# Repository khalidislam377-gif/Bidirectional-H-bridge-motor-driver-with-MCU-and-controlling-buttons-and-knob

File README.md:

# Bidirectional-H-bridge-motor-driver-with-MCU-and-controlling-buttons-and-knob
`An embedded control architecture and discrete power stage for bidirectional DC motor regulation, featuring finite-state machine logic, real-time telemetry, and a Rev 1.0 hardware post-mortem.`

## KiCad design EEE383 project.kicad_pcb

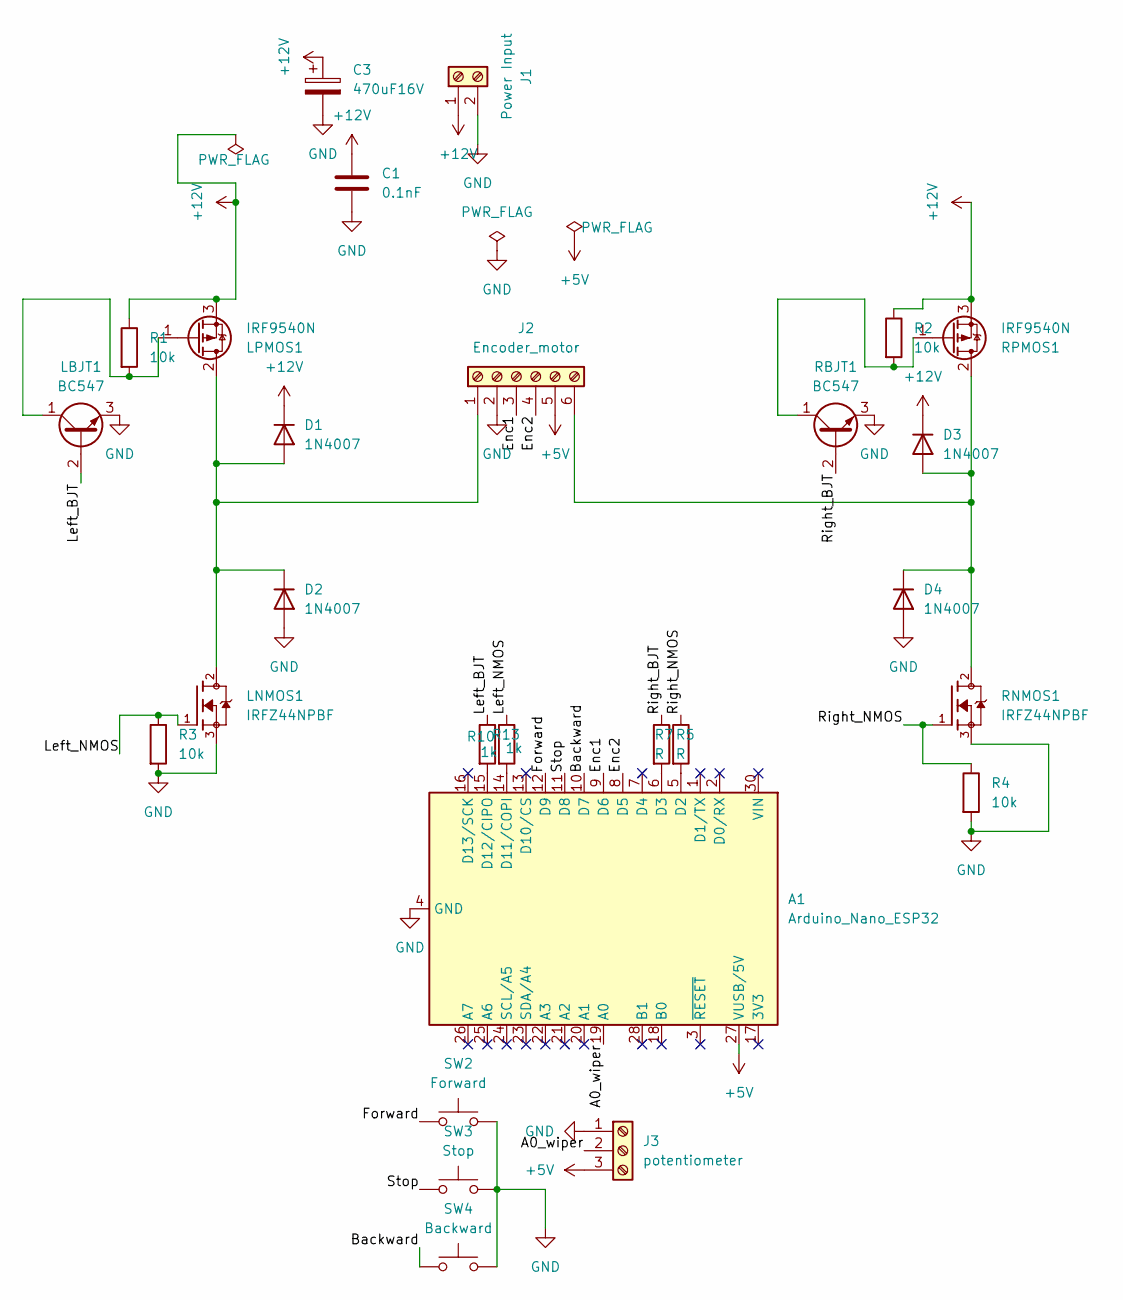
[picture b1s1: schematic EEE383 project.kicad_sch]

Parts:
A1: Arduino_Nano_ESP32; Arduino_Nano
C1: 0.1nF; C_Axial_L3.8mm_D2.6mm_P7.50mm_Horizontal
C3: 470uF16V; C_Radial_D6.3mm_H5.0mm_P2.50mm
D1, D2, D3, D4: 1N4007; D_DO-41_SOD81_P10.16mm_Horizontal
J1: Power Input; JST_PH_B2B-PH-K_1x02_P2.00mm_Vertical
J2: Encoder_motor; JST_PH_S6B-PH-K_1x06_P2.00mm_Horizontal
J3: potentiometer; BPot
LBJT1: BC547; TO-92_Inline
LNMOS1: IRFZ44NPBF; TO254P1016X419X2286-3; PARTREV 09/21/10
LPMOS1: IRF9540N; TO-220-3_Vertical
R1, R2, R3, R4: 10k; R_Axial_DIN0204_L3.6mm_D1.6mm_P7.62mm_Horizontal
R5, R7: R; R_Axial_DIN0204_L3.6mm_D1.6mm_P7.62mm_Horizontal
R10, R13: 1k; R_Axial_DIN0204_L3.6mm_D1.6mm_P7.62mm_Horizontal
RBJT1: BC547; TO-92_Inline
RNMOS1: IRFZ44NPBF; TO254P1016X419X2286-3; PARTREV 09/21/10
RPMOS1: IRF9540N; TO-220-3_Vertical
SW2: Forward; SW_PUSH_6mm_H4.3mm
SW3: Stop; SW_PUSH_6mm_H4.3mm
SW4: Backward; SW_PUSH_6mm_H4.3mm

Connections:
+5V: A1.27 (VUSB/5V), J2.5, J3.3
+12V: C1.1, C3.1, D1.1 (K), D3.1 (K), J1.1, LPMOS1.3 (S), R1.1, R2.1, RPMOS1.3 (S)
/A0_wiper: A1.19 (A0), J3.2
/Backward: A1.10 (D7), SW4.1
/Enc1: A1.9 (D6), J2.3
/Enc2: A1.8 (D5), J2.4
/Forward: A1.12 (D9), SW2.1
/Left_BJT: LBJT1.2 (B), R10.1
/Left_NMOS: LNMOS1.1, R3.1, R13.1
/Right_BJT: R7.1, RBJT1.2 (B)
/Right_NMOS: R4.1, R5.1, RNMOS1.1
/Stop: A1.11 (D8), SW3.1
GND: A1.4 (GND), A1.29 (GND), C1.2, C3.2, D2.2 (A), D4.2 (A), J1.2, J2.2, J3.1, LBJT1.3 (E), LNMOS1.3, R3.2, R4.2, RBJT1.3 (E), RNMOS1.3, SW2.2, SW3.2, SW4.2
unnamed: A1.5 (D2), R5.2
unnamed: A1.6 (D3), R7.2
unnamed: A1.14 (D11/COPI), R13.2
unnamed: A1.15 (D12/CIPO), R10.2
unnamed: D1.2 (A), D2.1 (K), J2.1, LNMOS1.2, LPMOS1.2 (D)
unnamed: D3.2 (A), D4.1 (K), J2.6, RNMOS1.2, RPMOS1.2 (D)
unnamed: LBJT1.1 (C), LPMOS1.1 (G), R1.2
unnamed: R2.2, RBJT1.1 (C), RPMOS1.1 (G)

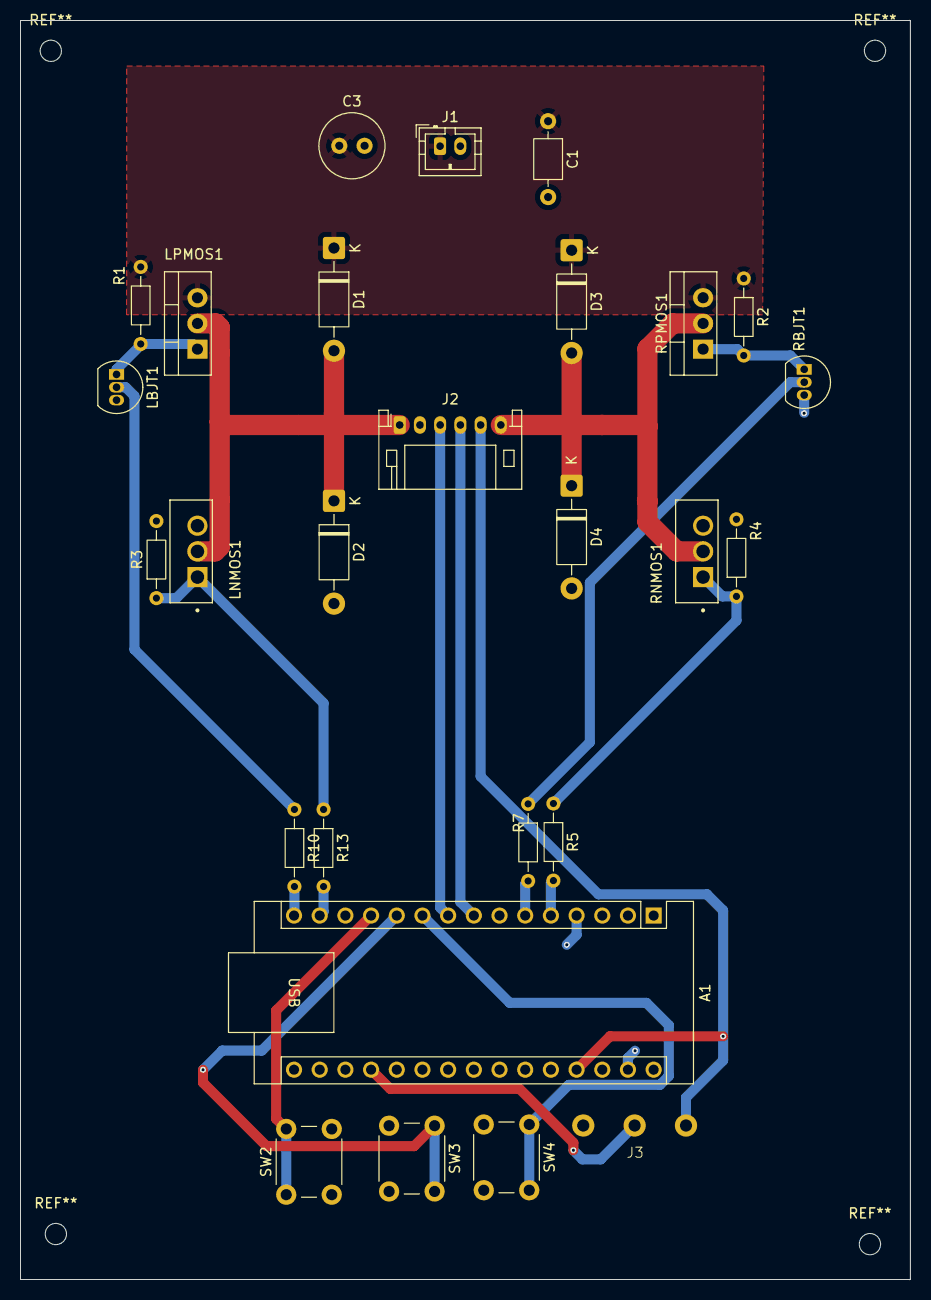
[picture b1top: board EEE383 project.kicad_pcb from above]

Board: 2 copper layers, 88.0 x 124.5 mm, 27 parts (0 on the bottom side), 21 nets.
